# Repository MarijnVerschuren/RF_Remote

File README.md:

# RF_Remote
A simple 433.92 MHz remote

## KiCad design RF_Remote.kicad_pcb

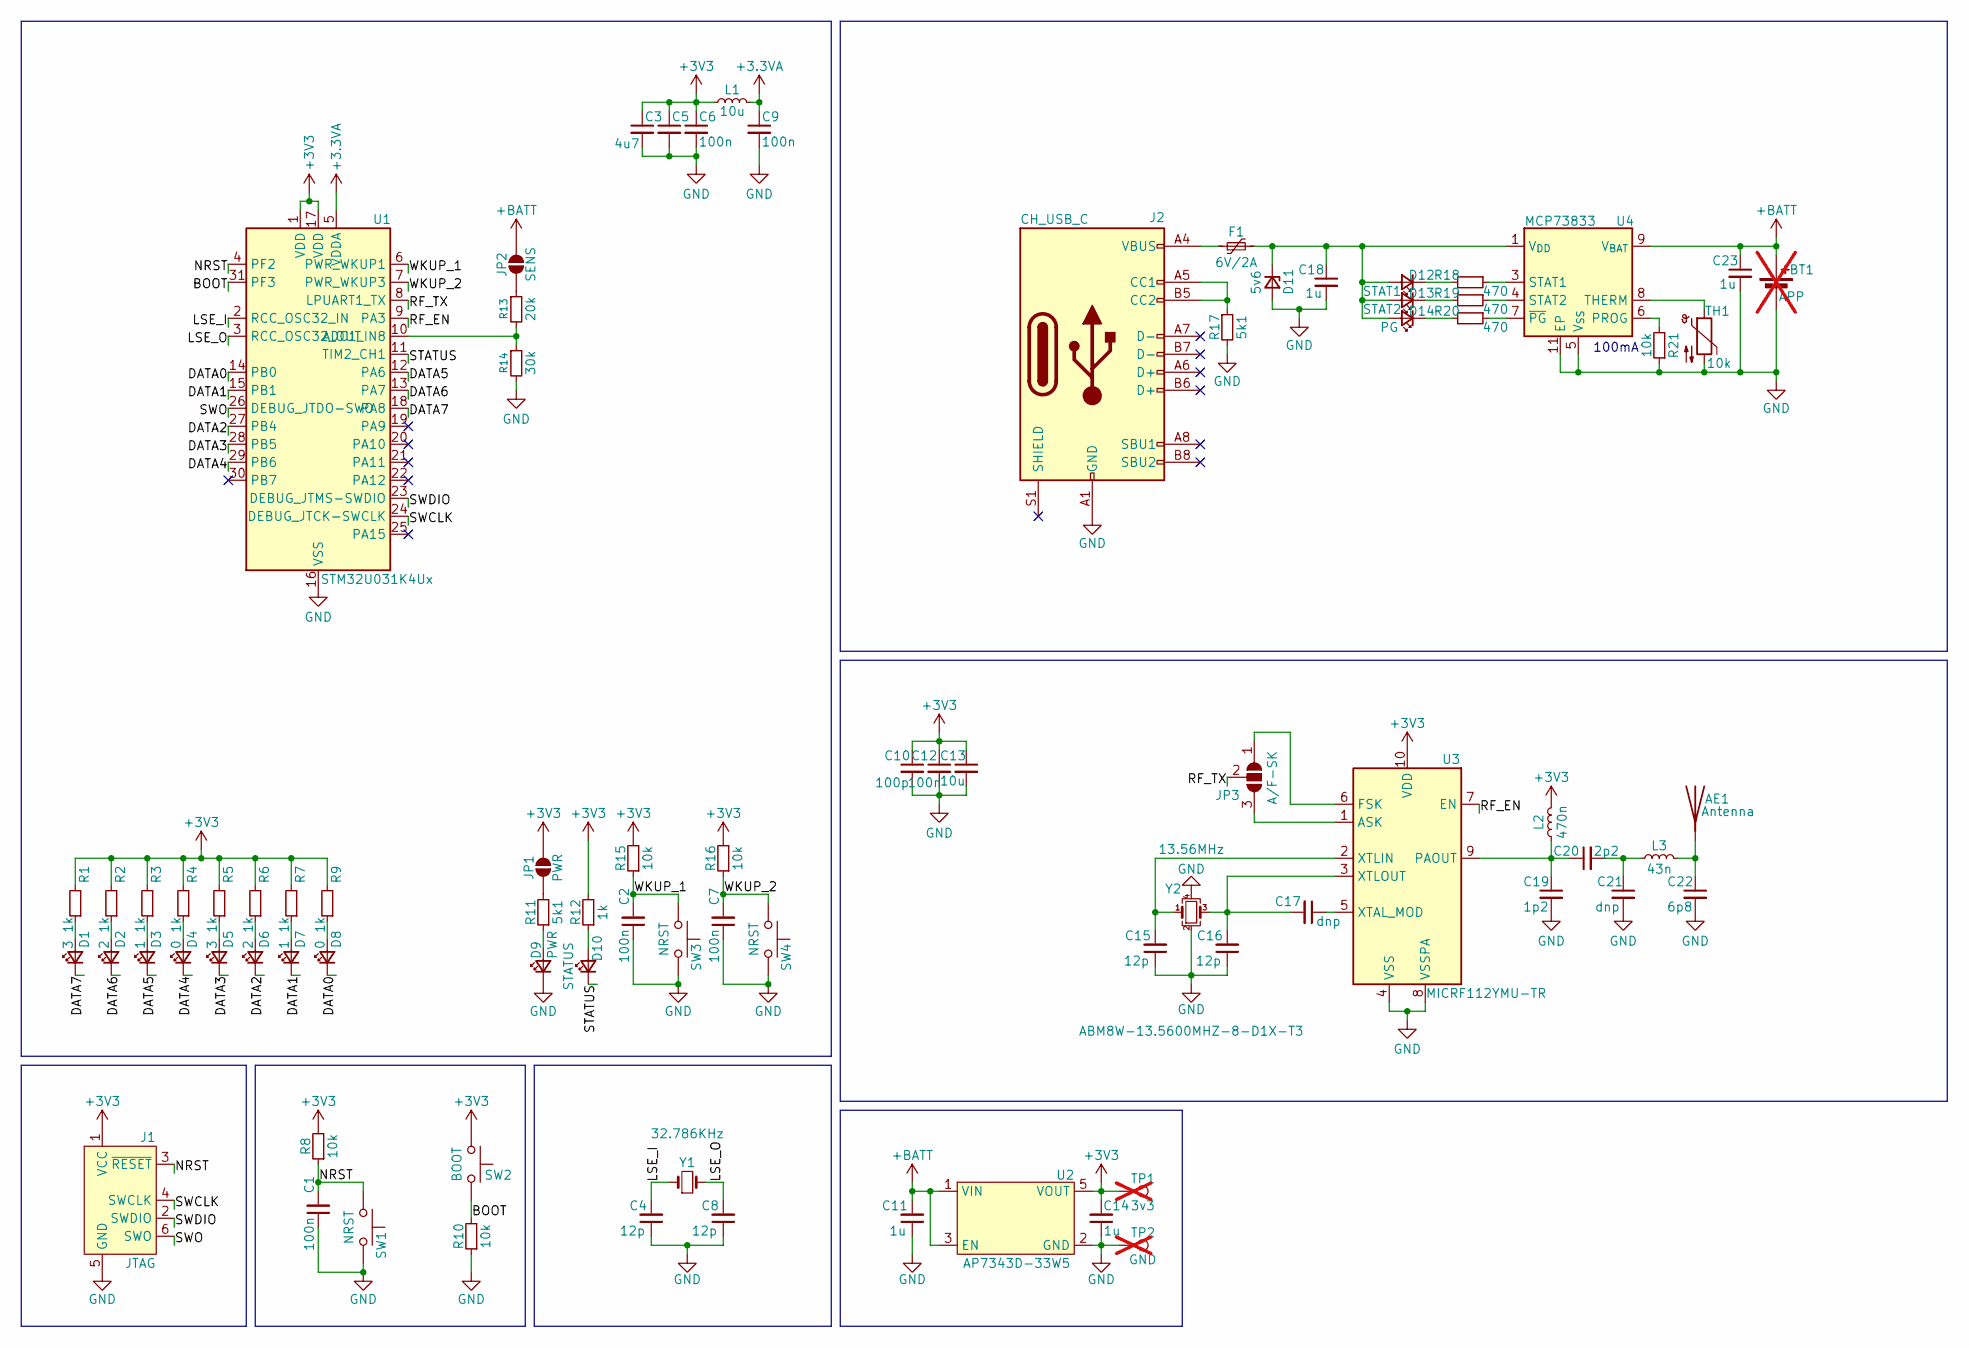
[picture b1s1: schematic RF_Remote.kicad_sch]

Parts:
AE1: Antenna; TestPoint_THTPad_D1.0mm_Drill0.5mm
BT1: APP; PinHeader_1x02_P2.54mm_Vertical; not fitted
C1, C2, C5, C6, C7, C9, C12: 100n; C_0603_1608Metric
C3: 4u7; C_0603_1608Metric
C4, C8, C15, C16: 12p; C_0603_1608Metric
C10: 100p; C_0603_1608Metric
C11, C14: 1u; C_0603_1608Metric
C13: 10u; C_0603_1608Metric
C17, C21: dnp; C_0603_1608Metric
C18, C23: 1u; C_0603_1608Metric; mouser 963-MLAST168SB7105KT
C19: 1p2; C_0603_1608Metric
C20: 2p2; C_0603_1608Metric
C22: 6p8; C_0603_1608Metric
D1, D5: 3; LED_0603_1608Metric; mouser 710-150060AS75000
D2, D6: 2; LED_0603_1608Metric; mouser 710-150060AS75000
D3, D7: 1; LED_0603_1608Metric; mouser 710-150060AS75000
D4, D8: 0; LED_0603_1608Metric; mouser 710-150060AS75000
D9: PWR; LED_0603_1608Metric; mouser 710-150060AS75000
D10: STATUS; LED_0603_1608Metric; mouser 710-150060AS75000
D11: 5v6; D_SOD-123; mouser 78-BZT52C5V6-E3-08
D12: STAT1; LED_0603_1608Metric; mouser 710-150060AS75000
D13: STAT2; LED_0603_1608Metric; mouser 710-150060AS75000
D14: PG; LED_0603_1608Metric; mouser 710-150060RS75000
F1: 6V/2A; Fuse_1206_3216Metric; mouser 504-PTS18126V260
J1: JTAG; Tag-Connect_TC2030-IDC-FP_2x03_P1.27mm_Vertical
J2: CH_USB_C; USB_C_Receptacle_HCTL_HC-TYPE-C-16P-01A
JP1: PWR; SolderJumper-2_P1.3mm_Open_TrianglePad1.0x1.5mm
JP2: SENS; SolderJumper-2_P1.3mm_Open_TrianglePad1.0x1.5mm
JP3: A/F-SK; SolderJumper-3_P2.0mm_Open_TrianglePad1.0x1.5mm_NumberLabels
L1: 10u; L_0805_2012Metric
L2: 470n; L_0805_2012Metric
L3: 43n; L_0805_2012Metric
R1, R2, R3, R4, R5, R6, R7, R9, R12: 1k; R_0603_1608Metric
R8, R10, R15, R16: 10k; R_0603_1608Metric
R11: 5k1; R_0603_1608Metric
R13: 20k; R_0603_1608Metric
R14: 30k; R_0603_1608Metric
R17: 5k1; R_0603_1608Metric; LCSC C23186
R18, R19, R20: 470; R_0603_1608Metric; LCSC C23186
R21: 10k; R_0603_1608Metric; LCSC C23186
SW1, SW3, SW4: NRST; SW_SPST_PTS810; LCSC C2681476
SW2: BOOT; SW_SPST_PTS810; LCSC C2681476
TH1: 10k; R_0603_1608Metric; mouser 667-ERT-J1VR103J
TP1: 3v3; TestPoint_Pad_D1.5mm; not fitted
TP2: GND; TestPoint_Pad_D1.5mm; not fitted
U1: STM32U031K4Ux; QFN-32-1EP_5x5mm_P0.5mm_EP3.45x3.45mm
U2: AP7343D-33W5; SOT-25
U3: MICRF112YMU-TR; DFN-10-1EP_2.6x2.6mm_P0.5mm_EP1.3x2.2mm
U4: MCP73833; DFN-10-1EP_3x3mm_P0.5mm_EP1.58x2.35mm; mouser 579-MCP73833T-AMI/MF
Y1: 32.786KHz; Crystal_SMD_3215-2Pin_3.2x1.5mm
Y2: 13.56MHz; Crystal_SMD_3225-4Pin_3.2x2.5mm

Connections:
+3.3VA: C9.1, L1.2, U1.5 (VDDA)
+3V3: C3.1, C5.1, C6.1, C10.1, C12.1, C13.1, C14.2, J1.1 (VCC), JP1.2 (B), L1.1, L2.2, R1.2, R2.2, R3.2, R4.2, R5.2, R6.2, R7.2, R8.2, R9.2, R12.2, R15.2, R16.2, SW2.1, TP1.1, U1.1 (VDD), U1.17 (VDD), U2.5 (VOUT), U3.10 (VDD)
+BATT: BT1.1 (+), C11.2, C23.1, JP2.2 (B), U2.1 (VIN), U2.3 (EN), U4.9 (V_{BAT}), U4.10 (V_{BAT})
/BOOT: R10.2, SW2.2, U1.31 (PF3)
/DATA0: D8.1 (K), U1.14 (PB0)
/DATA1: D7.1 (K), U1.15 (PB1)
/DATA2: D6.1 (K), U1.27 (PB4)
/DATA3: D5.1 (K), U1.28 (PB5)
/DATA4: D4.1 (K), U1.29 (PB6)
/DATA5: D3.1 (K), U1.12 (PA6)
/DATA6: D2.1 (K), U1.13 (PA7)
/DATA7: D1.1 (K), U1.18 (PA8)
/LSE_I: C4.2, U1.2 (RCC_OSC32_IN), Y1.1
/LSE_O: C8.2, U1.3 (RCC_OSC32_OUT), Y1.2
/NRST: C1.2, J1.3 (~RESET), R8.1, SW1.1, U1.4 (PF2)
/RF_EN: U1.9 (PA3), U3.7 (EN)
/RF_TX: JP3.2 (C), U1.8 (LPUART1_TX)
/STATUS: D10.1 (K), U1.11 (TIM2_CH1)
/SWCLK: J1.4 (SWCLK), U1.24 (DEBUG_JTCK-SWCLK)
/SWDIO: J1.2 (SWDIO), U1.23 (DEBUG_JTMS-SWDIO)
/SWO: J1.6 (SWO), U1.26 (DEBUG_JTDO-SWO)
/WKUP_1: C2.2, R15.1, SW3.1, U1.6 (PWR_WKUP1)
/WKUP_2: C7.2, R16.1, SW4.1, U1.7 (PWR_WKUP3)
GND: BT1.2 (-), C1.1, C2.1, C3.2, C4.1, C5.2, C6.2, C7.1, C8.1, C9.2, C10.2, C11.1, C12.2, C13.2, C14.1, C15.1, C16.1, C18.2, C19.2, C21.2, C22.2, C23.2, D9.1 (K), D11.2 (A), J1.5 (GND), J2.A1 (GND), J2.A12 (GND), J2.B1 (GND), J2.B12 (GND), R10.1, R14.2, R17.2, R21.1, SW1.2, SW3.2, SW4.2, TH1.2, TP2.1, U1.16 (VSS), U1.32 (VSS), U1.33 (VSS), U2.2 (GND), U3.4 (VSS), U3.8 (VSSPA), U4.5 (V_{SS}), U4.11 (EP), Y2.2, Y2.4
unnamed: AE1.1 (A), C22.1, L3.2
unnamed: C20.2, C21.1, L3.1
unnamed: D1.2 (A), R1.1
unnamed: D2.2 (A), R2.1
unnamed: D3.2 (A), R3.1
unnamed: D4.2 (A), R4.1
unnamed: D5.2 (A), R5.1
unnamed: D6.2 (A), R6.1
unnamed: D7.2 (A), R7.1
unnamed: D8.2 (A), R9.1
unnamed: D9.2 (A), R11.1
unnamed: D10.2 (A), R12.1
unnamed: C18.1, D11.1 (K), D12.2 (A), D13.2 (A), D14.2 (A), F1.2, U4.1 (V_{DD}), U4.2 (V_{DD})
unnamed: D12.1 (K), R18.2
unnamed: D13.1 (K), R19.2
unnamed: D14.1 (K), R20.2
unnamed: F1.1, J2.A4 (VBUS), J2.A9 (VBUS), J2.B4 (VBUS), J2.B9 (VBUS)
unnamed: J2.A5 (CC1), J2.B5 (CC2), R17.1
unnamed: JP1.1 (A), R11.2
unnamed: JP2.1 (A), R13.1
unnamed: JP3.1 (A), U3.6 (FSK)
unnamed: JP3.3 (B), U3.1 (ASK)
unnamed: R13.2, R14.1, U1.10 (ADC1_IN8)
unnamed: C19.1, C20.1, L2.1, U3.9 (PAOUT)
unnamed: C17.1, U3.5 (XTAL_MOD)
unnamed: C15.2, U3.2 (XTLIN), Y2.1
unnamed: C16.2, C17.2, U3.3 (XTLOUT), Y2.3
unnamed: R21.2, U4.6 (PROG)
unnamed: R18.1, U4.3 (STAT1)
unnamed: R19.1, U4.4 (STAT2)
unnamed: TH1.1, U4.8 (THERM)
unnamed: R20.1, U4.7 (~PG)

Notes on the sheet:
100mA

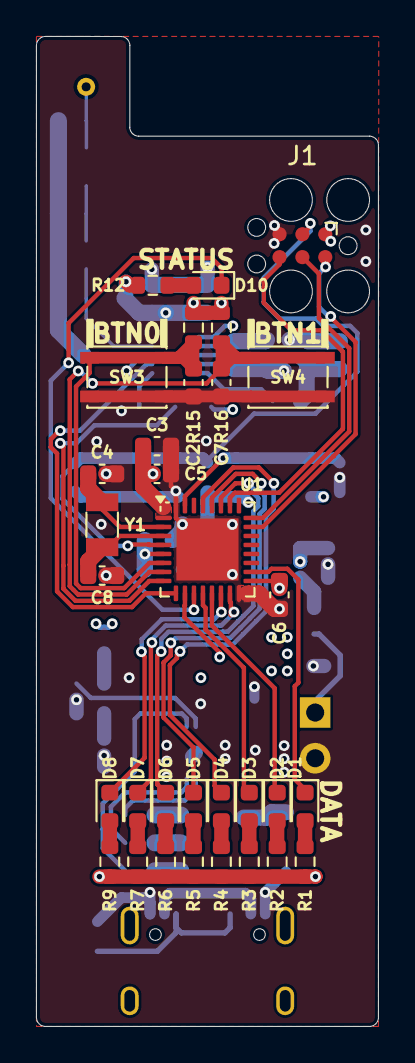
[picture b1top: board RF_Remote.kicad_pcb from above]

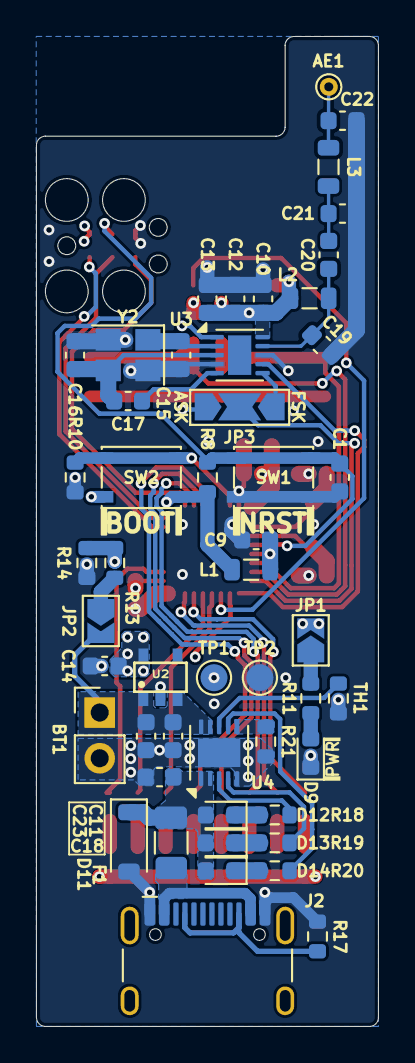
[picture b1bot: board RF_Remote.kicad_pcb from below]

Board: 4 copper layers, 19.0 x 55.0 mm, 82 parts (50 on the bottom side), 56 nets.

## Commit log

2025-04-26 Progress
2025-04-27 Routing progress
2025-04-29 Layout progress
2025-05-01 Layout v1
2025-05-03 Cleaned up layout
